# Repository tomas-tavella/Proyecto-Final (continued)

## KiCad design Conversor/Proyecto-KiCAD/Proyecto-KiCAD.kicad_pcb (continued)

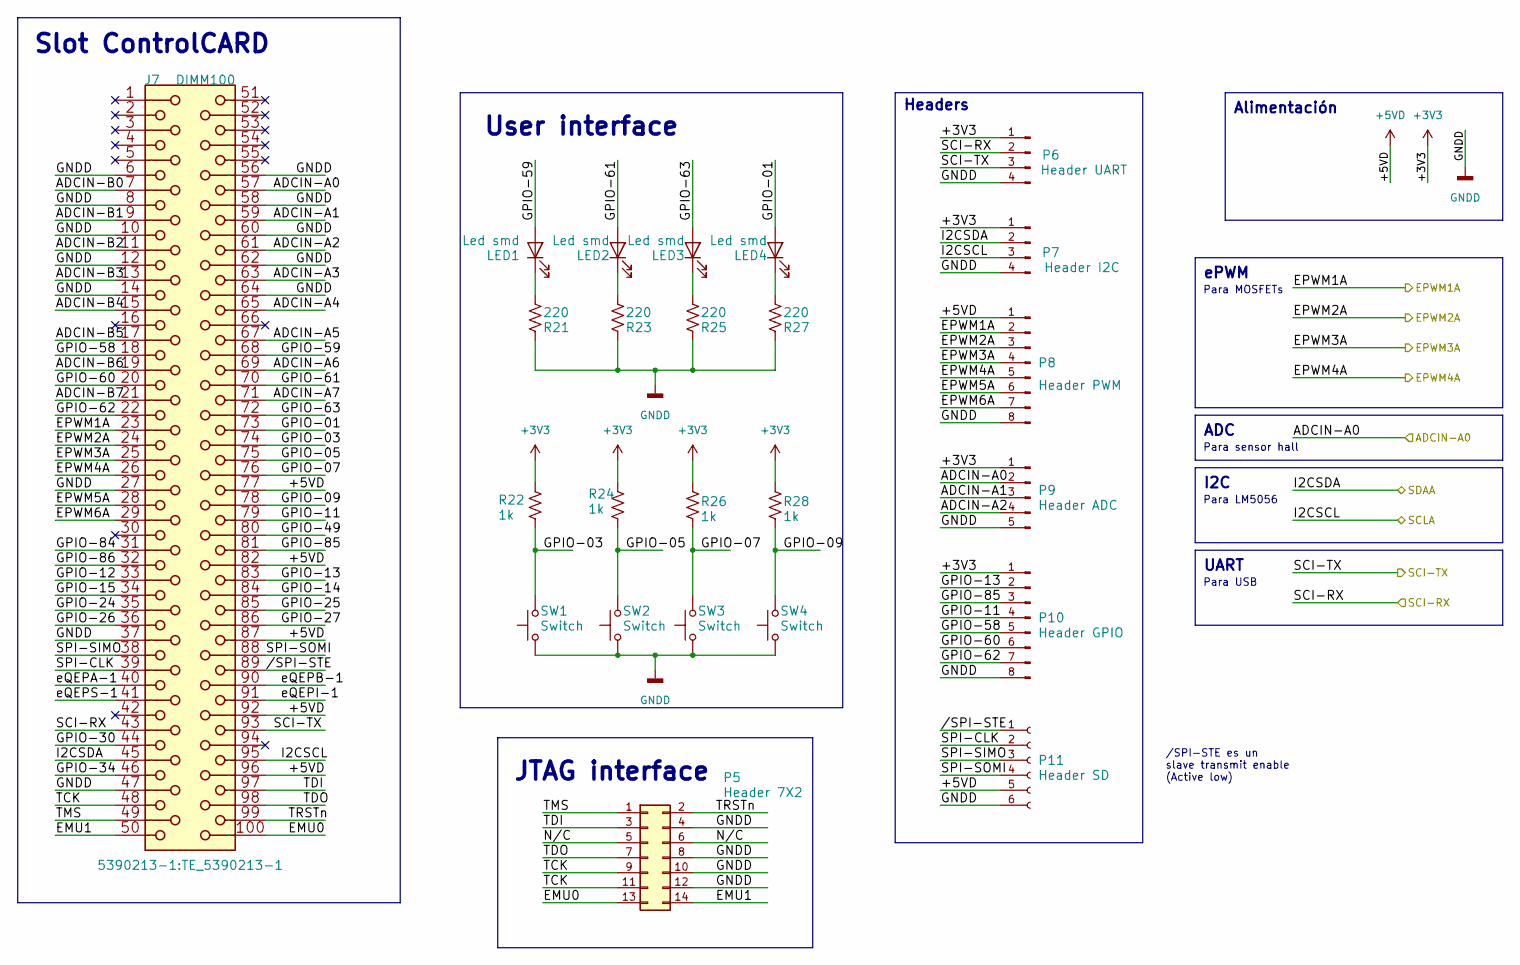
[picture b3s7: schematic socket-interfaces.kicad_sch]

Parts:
J7: DIMM100; TE_5390213-1
LED1, LED2, LED3, LED4: Led smd; D_1206_3216Metric_Pad1.42x1.75mm_HandSolder
P5: Header 7X2; PinSocket_2x07_P2.54mm_Vertical
P6: Header UART; PinHeader_1x04_P2.54mm_Vertical
P7: Header I2C; PinHeader_1x04_P2.54mm_Vertical
P8: Header PWM; PinHeader_1x08_P2.54mm_Vertical
P9: Header ADC; PinHeader_1x05_P2.54mm_Vertical
P10: Header GPIO; PinHeader_1x08_P2.54mm_Vertical
P11: Header SD; PinSocket_1x06_P2.54mm_Horizontal
R21, R23, R25, R27: 220; R_1206_3216Metric_Pad1.30x1.75mm_HandSolder
R22, R24, R26, R28: 1k; R_1206_3216Metric_Pad1.30x1.75mm_HandSolder
SW1, SW2, SW3, SW4: Switch; SW_PUSH_6mm

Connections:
+3V3: P6.1, P7.1, P9.1, P10.1, R22.2, R24.2, R26.2, R28.2; also elsewhere on the board
+5VD: J7.77 (p77), J7.82 (p82), J7.87 (p87), J7.92 (p92), J7.96 (p96), P8.1, P11.5; also elsewhere on the board
/Drivers y Optos/PWM1: J7.23 (p23), P8.2; also elsewhere on the board
/Drivers y Optos/PWM2: J7.24 (p24), P8.3; also elsewhere on the board
/Drivers y Optos//PWM3: J7.25 (p25), P8.4; also elsewhere on the board
/Drivers y Optos//PWM4: J7.26 (p26), P8.5; also elsewhere on the board
/Placa DSP/Socket Interfaces/ADCIN-A0: J7.57 (p57), P9.2; also elsewhere on the board
/Placa DSP/Socket Interfaces/ADCIN-A1: J7.59 (p59), P9.3
/Placa DSP/Socket Interfaces/ADCIN-A2: J7.61 (p61), P9.4
/Placa DSP/Socket Interfaces/ADCIN-A3: J7.63 (p63)
/Placa DSP/Socket Interfaces/ADCIN-A4: J7.65 (p65)
/Placa DSP/Socket Interfaces/ADCIN-A5: J7.67 (p67)
/Placa DSP/Socket Interfaces/ADCIN-A6: J7.69 (p69)
/Placa DSP/Socket Interfaces/ADCIN-A7: J7.71 (p71)
/Placa DSP/Socket Interfaces/ADCIN-B0: J7.7 (p7)
/Placa DSP/Socket Interfaces/ADCIN-B1: J7.9 (p9)
/Placa DSP/Socket Interfaces/ADCIN-B2: J7.11 (p11)
/Placa DSP/Socket Interfaces/ADCIN-B3: J7.13 (p13)
/Placa DSP/Socket Interfaces/ADCIN-B4: J7.15 (p15)
/Placa DSP/Socket Interfaces/ADCIN-B5: J7.17 (p17)
/Placa DSP/Socket Interfaces/ADCIN-B6: J7.19 (p19)
/Placa DSP/Socket Interfaces/ADCIN-B7: J7.21 (p21)
/Placa DSP/Socket Interfaces/EMU0: J7.100 (p100), P5.13
/Placa DSP/Socket Interfaces/EMU1: J7.50 (p50), P5.14
/Placa DSP/Socket Interfaces/EPWM5A: J7.28 (p28), P8.6
/Placa DSP/Socket Interfaces/EPWM6A: J7.29 (p29), P8.7
/Placa DSP/Socket Interfaces/GPIO-01: J7.73 (p73), LED4.2 (A)
/Placa DSP/Socket Interfaces/GPIO-03: J7.74 (p74), R22.1, SW1.2
/Placa DSP/Socket Interfaces/GPIO-05: J7.75 (p75), R24.1, SW2.2
/Placa DSP/Socket Interfaces/GPIO-07: J7.76 (p76), R26.1, SW3.2
/Placa DSP/Socket Interfaces/GPIO-09: J7.78 (p78), R28.1, SW4.2
/Placa DSP/Socket Interfaces/GPIO-11: J7.79 (p79), P10.4
/Placa DSP/Socket Interfaces/GPIO-12: J7.33 (p33)
/Placa DSP/Socket Interfaces/GPIO-13: J7.83 (p83), P10.2
/Placa DSP/Socket Interfaces/GPIO-14: J7.84 (p84)
/Placa DSP/Socket Interfaces/GPIO-15: J7.34 (p34)
/Placa DSP/Socket Interfaces/GPIO-24: J7.35 (p35)
/Placa DSP/Socket Interfaces/GPIO-25: J7.85 (p85)
/Placa DSP/Socket Interfaces/GPIO-26: J7.36 (p36)
/Placa DSP/Socket Interfaces/GPIO-27: J7.86 (p86)
/Placa DSP/Socket Interfaces/GPIO-30: J7.44 (p44)
/Placa DSP/Socket Interfaces/GPIO-34: J7.46 (p46)
/Placa DSP/Socket Interfaces/GPIO-49: J7.80 (p80)
/Placa DSP/Socket Interfaces/GPIO-58: J7.18 (p18), P10.5
/Placa DSP/Socket Interfaces/GPIO-59: J7.68 (p68), LED1.2 (A)
/Placa DSP/Socket Interfaces/GPIO-60: J7.20 (p20), P10.6
/Placa DSP/Socket Interfaces/GPIO-61: J7.70 (p70), LED2.2 (A)
/Placa DSP/Socket Interfaces/GPIO-62: J7.22 (p22), P10.7
/Placa DSP/Socket Interfaces/GPIO-63: J7.72 (p72), LED3.2 (A)
/Placa DSP/Socket Interfaces/GPIO-84: J7.31 (p31)
/Placa DSP/Socket Interfaces/GPIO-85: J7.81 (p81), P10.3
/Placa DSP/Socket Interfaces/GPIO-86: J7.32 (p32)
/Placa DSP/Socket Interfaces/I2CSCL: J7.95 (p95), P7.3; also elsewhere on the board
/Placa DSP/Socket Interfaces/I2CSDA: J7.45 (p45), P7.2; also elsewhere on the board
/Placa DSP/Socket Interfaces/SCI-RX: J7.43 (p43), P6.2; also elsewhere on the board
/Placa DSP/Socket Interfaces/SCI-TX: J7.93 (p93), P6.3; also elsewhere on the board
/Placa DSP/Socket Interfaces/SPI-CLK: J7.39 (p39), P11.2
/Placa DSP/Socket Interfaces/SPI-SIMO: J7.38 (p38), P11.3
/Placa DSP/Socket Interfaces/SPI-SOMI: J7.88 (p88), P11.4
/Placa DSP/Socket Interfaces/TCK: J7.48 (p48), P5.9, P5.11
/Placa DSP/Socket Interfaces/TDI: J7.97 (p97), P5.3
/Placa DSP/Socket Interfaces/TDO: J7.98 (p98), P5.7
/Placa DSP/Socket Interfaces/TMS: J7.49 (p49), P5.1
/Placa DSP/Socket Interfaces/TRSTn: J7.99 (p99), P5.2
/Placa DSP/Socket Interfaces/eQEPA-1: J7.40 (p40)
/Placa DSP/Socket Interfaces/eQEPB-1: J7.90 (p90)
/Placa DSP/Socket Interfaces/eQEPI-1: J7.91 (p91)
/Placa DSP/Socket Interfaces/eQEPS-1: J7.41 (p41)
/Placa DSP/Socket Interfaces//SPI-STE: J7.89 (p89), P11.1
GNDD: J7.6 (p6), J7.8 (p8), J7.10 (p10), J7.12 (p12), J7.14 (p14), J7.27 (p27), J7.37 (p37), J7.47 (p47), J7.56 (p56), J7.58 (p58), J7.60 (p60), J7.62 (p62), J7.64 (p64), P5.4, P5.8, P5.10, P5.12, P6.4, P7.4, P8.8, P9.5, P10.8, P11.6, R21.2, R23.2, R25.2, R27.2, SW1.1, SW2.1, SW3.1, SW4.1; also elsewhere on the board
unnamed: LED1.1 (K), R21.1
unnamed: LED2.1 (K), R23.1
unnamed: LED3.1 (K), R25.1
unnamed: LED4.1 (K), R27.1

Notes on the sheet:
Para LM5056
UART
Para MOSFETs
Para USB
ADC
/SPI-STE es un slave transmit enable (Active low)
Headers
JTAG interface
Slot ControlCARD
I2C
Para sensor hall
ePWM
User interface
Alimentación

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
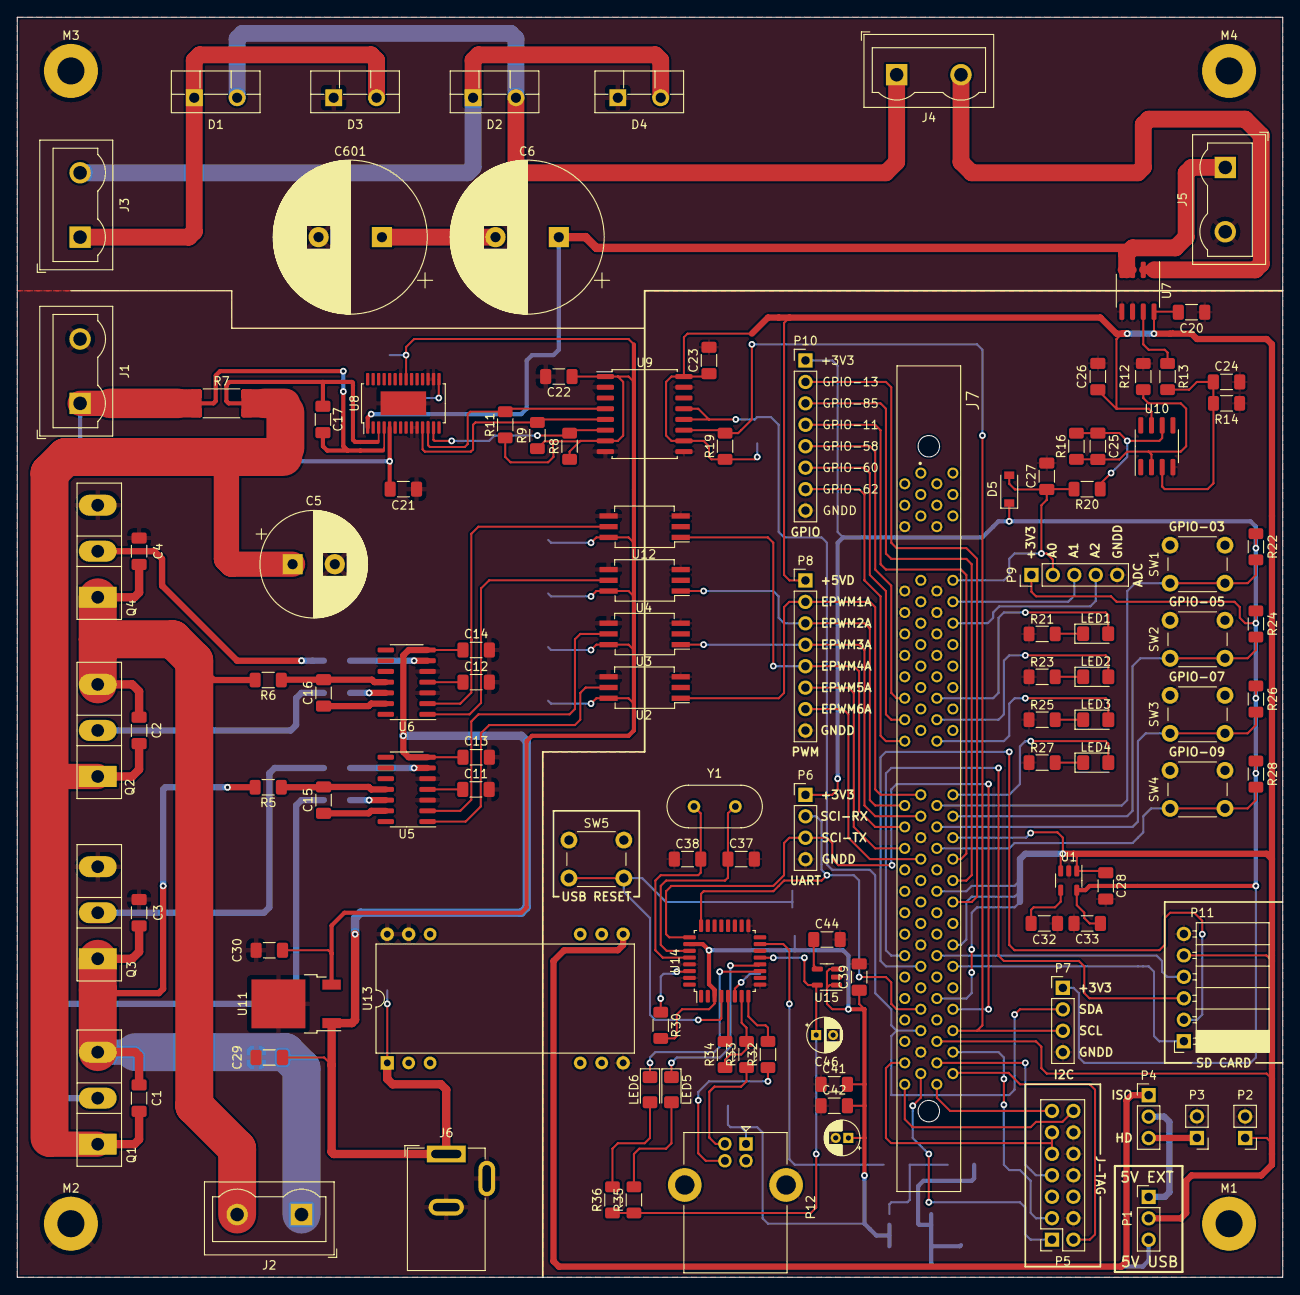
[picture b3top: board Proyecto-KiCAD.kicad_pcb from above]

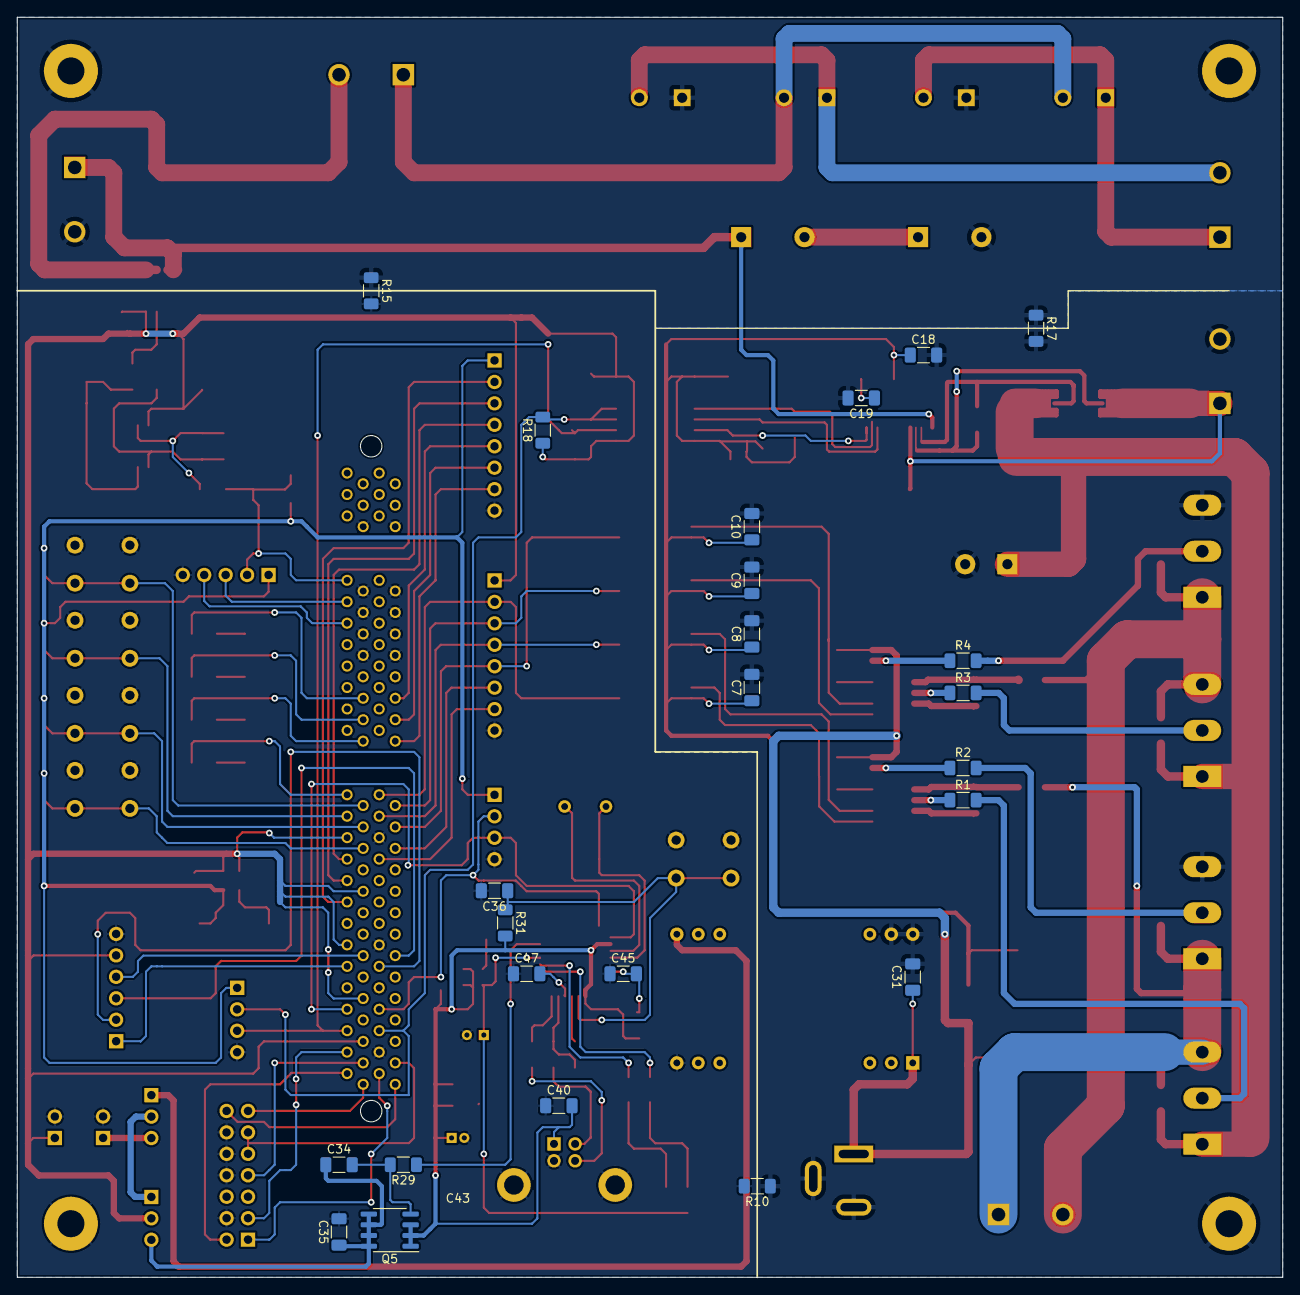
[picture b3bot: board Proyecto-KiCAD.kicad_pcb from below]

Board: 2 copper layers, 149.9 x 149.2 mm, 144 parts (24 on the bottom side), 110 nets.

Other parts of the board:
M1, M2, M3, M4: MountingHole_3.2mm_M3_Pad

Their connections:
GND1: M2.2; also elsewhere on the board
GND2: M3.3, M4.4; also elsewhere on the board
GNDD: M1.1; also elsewhere on the board

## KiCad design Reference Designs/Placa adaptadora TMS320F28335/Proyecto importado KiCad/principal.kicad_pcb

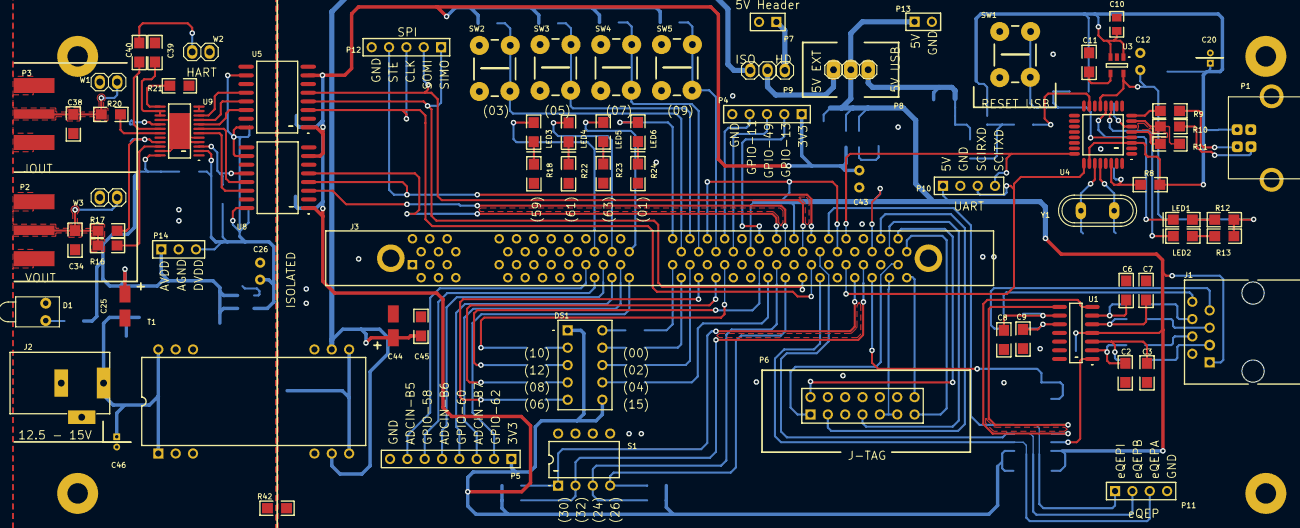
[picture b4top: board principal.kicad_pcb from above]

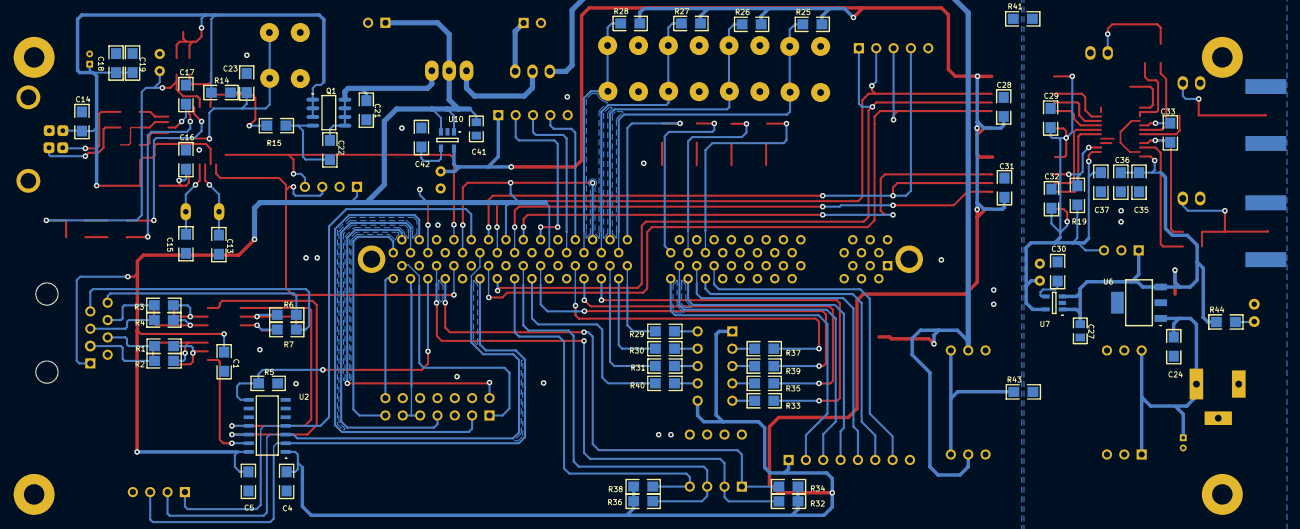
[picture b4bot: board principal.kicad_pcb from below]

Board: 2 copper layers, 137 parts (60 on the bottom side), 125 nets.

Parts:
C1, C2, C3, C4, C5, C6, C7, C8, C9, C11, C13, C14, C15, C16, C17, C18, C19, C21, C22, C23, C24, C28, C29, C30, C31, C32, C33, C34, C35, C36, C37, C38, C39, C40, C42, C45: Capacitor; C 1206
C10, C27, C41: Capacitor; 0805
C12, C26, C43: Tantalum capacitor; Tantalum
C20, C46: Capacitor polarzado; CAP4x7x1.5mm
C25, C44: Capacitor polarzado; Almn cap
D1: Typical RED GaAs LED; LED-1
DS1: 7.62 mm Black Surface Orange 7-Segment Display: C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; A
J1: RJ-45 connector, 8-pins, ethernet; 15-43-6588
J2: jack
J3: Vertical, DIMM 2P Low Insertion Force, 100 Positi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; 390213-1
LED1: LED red; LED 1206
LED2: LED green; LED 1206
LED3, LED5: Led green; LED 1206
LED4, LED6: Led yellow; LED 1206
P1: Conector USB tipo B; USBB
P2, P3: sma
P4, P12: Header, 5-Pin; HDR1X5
P5: Header, 8-Pin; HDR1X8
P6: Header, 7-Pin, Dual row; HDR2X7
P7, P13: Header, 2-Pin; HDR1X2
P8: Toggle sw
P9: Jumper 2
P10, P11: Header, 4-Pin; HDR1X4
P14: Header, 3-Pin; HDR1X3
Q1: HEXFET Power MOSFET; SO-8_L
R1, R2, R3, R4, R5, R6, R7, R8, R9, R10, R11, R12, R13, R14, R15, R16, R17, R18, R19, R20, R21, R22, R23, R24, R25, R26, R27, R28, R29, R30, R31, R32, R33, R34, R35, R36, R37, R38, R39, R40, R41, R42, R43, R44: Resistencia; R 1206
S1: DIP Switch; DIP-8
SW1, SW2, SW3, SW4, SW5: TACT SW
T1: DIL24
U1: Low Power Quad Operational Amplifier, 14-pin Narr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; M14A_N
U2: IC VOLT-LEVEL TRANSLATOR 14-SOIC; SOIC-14
U3, U7, U10: Single Output Low Noise LDO, 150 mA, Fixed 3.3 V 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; TI-DBV5_N
U4: USB UART Asynchronous Serial Data Transfer Chip, 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; LQFP-32_N
U5, U8: 150 Mbps 6 kVpk Low Power Quad Channels, Digital 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; DW0016A_N
U6: DCY4
U9: DAC8760; PWP
W1, W2, W3: Jumper Wire; Jumper
Y1: Cristal de 6Mhz; Y TRHU

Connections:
3V3: C4.2, C28.1, C31.1, C43.1, DS1.1, DS1.6, P4.1, P5.1, R25.2, R26.2, R27.2, R28.2, R32.1, R34.1, R36.1, R38.1, U2.1, U5.1, U5.7, U8.1, U8.7, U10.5
3V3OUT: C17.2, U4.6
5V: C1.2, C5.1, C41.1, J1.1, J3.77, J3.82, J3.87, J3.92, J3.96, P8.2, P10.1, P13.1, U1.4, U2.14, U10.1, U10.3
5V HEADER: P7.1, P9.3
5V SUPPLY: C44.1, C45.2, P9.1, T1.11, T1.14
5V USB: C21.1, C22.1, P8.1, Q1.5, Q1.6, Q1.7, Q1.8
+VSENSE: R16.2, U9.22
A: U1.1, U2.13
A+: J1.3, R2.2
A-: J1.4, R1.2
ADCIN-B5: J3.17, P5.7
ADCIN-B6: J3.19, P5.5
ADCIN-B7: J3.21, P5.3
AGND: C24.1, C25.2, C26.2, C27.1, C29.2, C30.2, C32.2, C34.2, C35.2, C36.2, C37.2, C38.2, C39.2, C46.2, D1.2, J2.2, J2.3, P2.2, P3.2, P14.2, R21.2, R41.2, R42.2, R43.1, U5.9, U5.15, U6.2, U6.4, U7.2, U8.9, U8.15, U9.1, U9.4, U9.5, U9.11, U9.12, U9.16, U9.23, U9.25, W1.2, W2.2, W3.2
AGND1: R43.2, T1.12, T1.13
ALARM#: R19.2, U8.12, U9.3
AVCC: C16.2, R8.2, U4.30
AVDD: C25.1, C27.2, C35.1, C36.1, P14.1, R44.2, U6.3, U7.1, U7.3, U9.24
B: U1.7, U2.12
B+: J1.5, R4.2
B-: J1.6, R3.2
CLR: U8.14, U9.6
CS#: U8.13, U9.7
DM: P1.2, R9.2
DP: P1.3, R10.2
DVDD: C26.1, C29.1, C32.1, C37.1, P14.3, R19.1, U5.10, U5.16, U7.5, U8.10, U8.16, U9.2
EMU0: J3.100, P6.13
EMU1: J3.50, P6.14
EQEPA-1: J3.40, P11.3, U2.2
EQEPB-1: J3.90, P11.2, U2.3
EQEPI-1: J3.91, P11.1, U2.4
EXTERN 5V: P8.3, P9.2
FA+: C3.2, R2.1, U1.3
FA-: C2.1, R1.1, U1.2
FB+: C7.2, R4.1, U1.5
FB-: C6.1, R3.1, U1.6
FZ+: C9.2, R7.1, U1.10
FZ-: C8.1, R6.1, U1.9
GND: C1.1, C2.2, C3.1, C4.1, C5.2, C6.2, C7.1, C8.2, C9.1, C10.2, C11.2, C12.2, C13.2, C14.2, C15.2, C16.1, C17.1, C18.1, C19.1, C20.2, C21.2, C23.2, C28.2, C31.2, C41.2, C42.2, C43.2, C44.2, C45.1, J1.2, J3.6, J3.8, J3.10, J3.12, J3.14, J3.27, J3.37, J3.47, J3.56, J3.58, J3.60, J3.62, J3.64, P1.0, P1.4, P4.5, P5.8, P6.4, P6.8, P6.10, P6.12, P7.2, P10.2, P11.4, P12.5, P13.2, R5.1, R18.2, R22.2, R23.2, R24.2, R41.1, R42.1, S1.5, S1.6, S1.7, S1.8, SW1.1, SW2.1, SW3.1, SW4.1, SW5.1, T1.10, T1.15, U1.11, U2.7, U3.2, U4.9, U4.14, U4.17, U4.29, U4.31, U5.2, U5.8, U8.2, U8.8, U10.2
GPIO-00: J3.23, R29.1
GPIO-01: J3.73, LED6.1
GPIO-02: J3.24, R30.1
GPIO-03: J3.74, R25.1, SW2.2
GPIO-04: J3.25, R31.1
GPIO-05: J3.75, R26.1, SW3.2
GPIO-06: J3.26, R33.1
GPIO-07: J3.76, R27.1, SW4.2
GPIO-08: J3.28, R35.1
GPIO-09: J3.78, R28.1, SW5.2
GPIO-10: J3.29, R37.1
GPIO-11: J3.79, P4.4
GPIO-12: J3.33, R39.1
GPIO-13: J3.83, P4.2
GPIO-15: J3.34, R40.1
GPIO-24: J3.35, R36.2, S1.3
GPIO-25: J3.85, U8.5
GPIO-26: J3.36, R38.2, S1.4
GPIO-27: J3.86, U8.3
GPIO-30: J3.44, R32.2, S1.1
GPIO-32: J3.45, R34.2, S1.2
GPIO-34: J3.46, R5.2, U2.8
GPIO-49: J3.80, P4.3
GPIO-58: J3.18, P5.6
GPIO-59: J3.68, LED3.1
GPIO-60: J3.20, P5.4
GPIO-61: J3.70, LED4.1
GPIO-62: J3.22, P5.2
GPIO-63: J3.72, LED5.1
HART-IN: C40.1, U9.18
IOUT: R20.2, U9.19
MISO: U5.12, U9.10
MOSI: U5.13, U9.9
NetC11_1: C11.1, U3.4
NetC22_2: C22.2, Q1.4, R15.2
NetC30_1: C30.1, U7.4
NetC33_2: C33.2, U9.17
NetC34_1: C34.1, P2.1, R16.1, R17.1, W3.1
NetC38_1: C38.1, P3.1, R20.1, W1.1
NetC40_2: C40.2, W2.1
NetC42_1: C42.1, U10.4
NetD1_1: D1.1, R44.1
NetDS1_2: DS1.2, R37.2
NetDS1_3: DS1.3, R39.2
NetDS1_4: DS1.4, R35.2
NetDS1_5: DS1.5, R33.2
NetDS1_7: DS1.7, R40.2
NetDS1_8: DS1.8, R31.2
NetDS1_9: DS1.9, R30.2
NetDS1_10: DS1.10, R29.2
NetLED1_1: LED1.1, R12.2
NetLED2_1: LED2.1, R13.2
NetLED3_2: LED3.2, R18.1
NetLED4_2: LED4.2, R22.1
NetLED5_2: LED5.2, R23.1
NetLED6_2: LED6.2, R24.1
NetR21_1: R21.1, U9.13
PWREN#: R15.1, U4.15
REFIN: C39.1, U9.14, U9.15
RESET#: C23.1, R14.1, SW1.2, U4.4
RSTOUT#: R11.1, U4.5
RXD: J3.93, P10.4, U4.24
RXLED#: LED2.2, U4.11
SCIRX-A: J3.43, P10.3, U4.25
SCLK: U5.14, U9.8
SPICLK-A: J3.39, P12.3, U5.3
SPISIMO-A: J3.38, P12.1, U5.4
SPISOMI-A: J3.88, P12.2, U5.5
SPISTE-A: J3.89, P12.4, U8.4
SUPPLY: C24.2, C46.1, J2.1, T1.1, T1.24, U6.1
TCK: J3.48, P6.9, P6.11
TDI: J3.97, P6.3
TDO: J3.98, P6.7
TMS: J3.49, P6.1
TRSTN: J3.99, P6.2
TXLED#: LED1.2, U4.12
U5V: C10.1, C14.1, C18.2, C19.2, C20.1, P1.1, Q1.1, Q1.2, Q1.3, R8.1, R14.2, U3.1, U3.3, U4.3, U4.26
USBDM: R9.1, U4.8
USBDP: R10.1, R11.2, U4.7
VCCIO: C12.1, R12.1, R13.1, U3.5, U4.13
VOUT: C33.1, R17.2, U9.21
XTIN: C13.1, U4.27, Y1.1
XTOUT: C15.1, U4.28, Y1.2
Z: U1.8, U2.11
Z+: J1.7, R7.2
Z-: J1.8, R6.2

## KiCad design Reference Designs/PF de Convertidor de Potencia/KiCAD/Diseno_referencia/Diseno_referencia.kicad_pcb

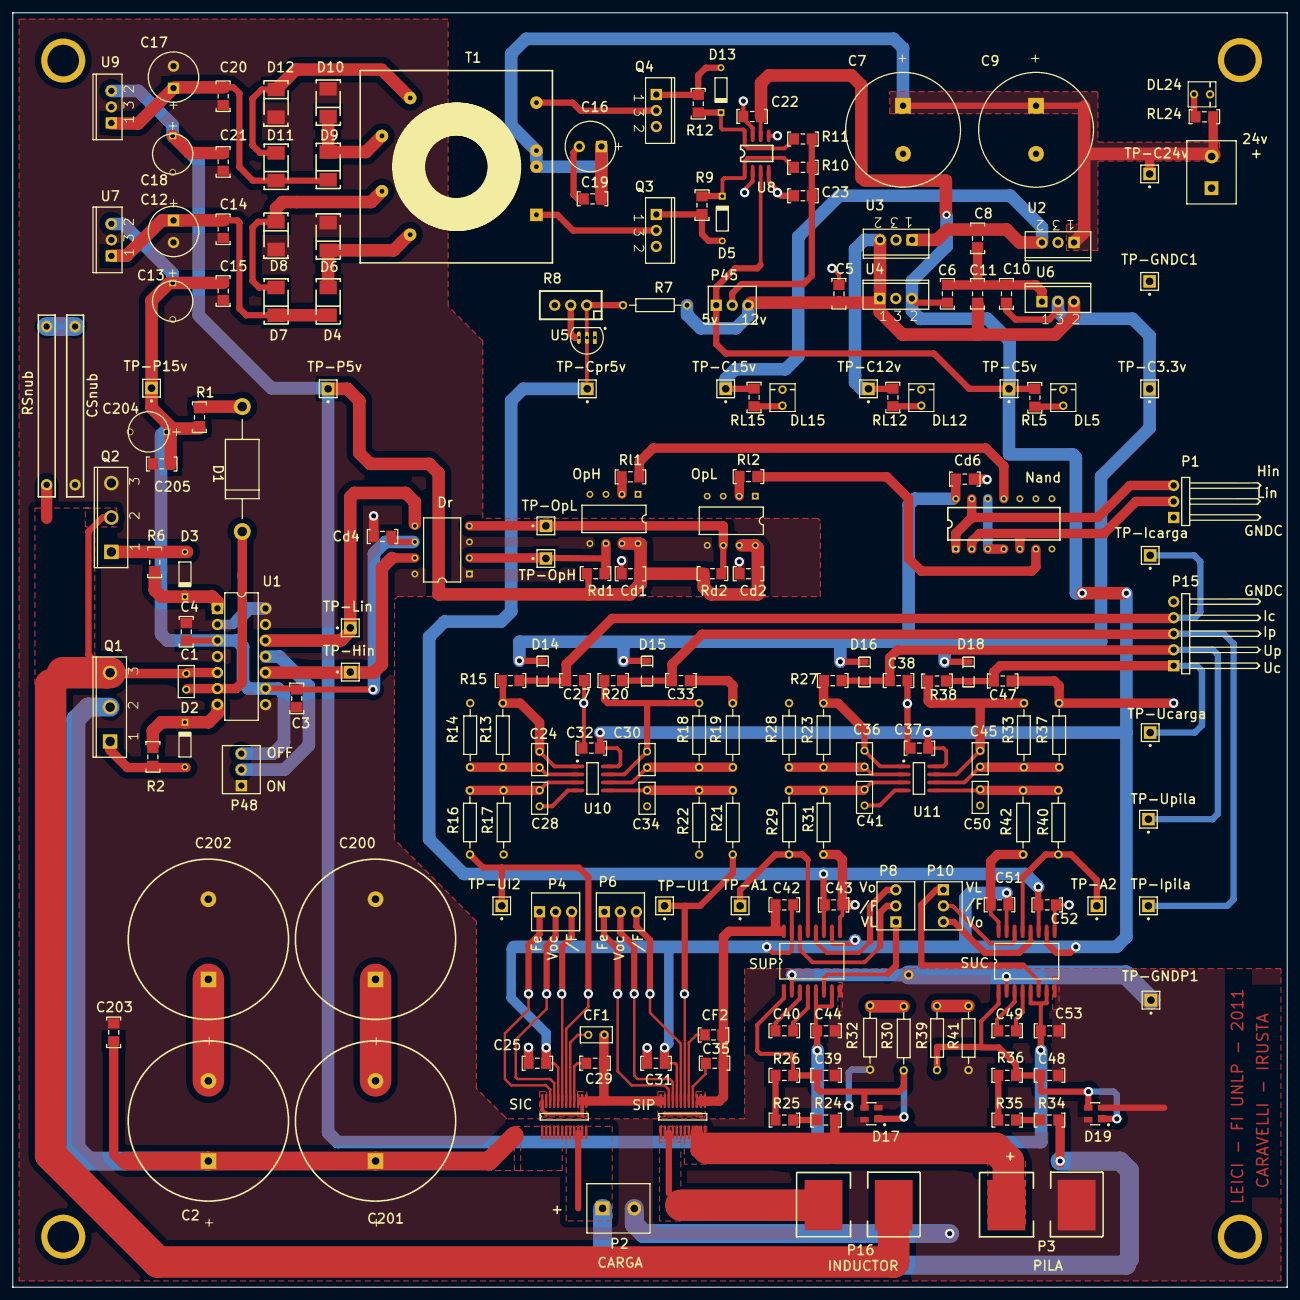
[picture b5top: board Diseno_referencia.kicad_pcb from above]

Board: 2 copper layers, 202.0 x 202.0 mm, 193 parts (0 on the bottom side), 102 nets.

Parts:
24v: Alimentacion 24v; HDR1X2-POT*
C1: CapBootstrap; RAD-0.1
C2, C200, C201, C202: Cap Pol1; RB12.7-25*
C3: Cap3; 8-1206
C4, C203, C205: Cap4; 8-1206
C5: Cap5; 8-1206
C6: Cap6; 8-1206
C7, C9: Cap Pol1; RB7.6-18.2*
C8: Cap8; 8-1206
C10: Cap10; 8-1206
C11: Cap11; 8-1206
C12, C16, C17: Cap Pol1; RB3.5-8*
C13, C18, C204: Cap Pol1; RB5.8-6.4*
C14: Cap14; 8-1206
C15: Cap15; 8-1206
C19: Cap19; 8-1206
C20: Cap20; 8-1206
C21: Cap21; 8-1206
C22: Cap22; 8-1206
C23: Cap23; 8-1206
C24: Cap24; RAD-0.1
C25: Cap25; 8-1206
C27: Cap27; 8-1206
C28: Cap28; RAD-0.1
C29: Cap29; 8-1206
C30: Cap30; RAD-0.1
C31: Cap31; 8-1206
C32: Cap32; 8-1206
C33: Cap33; 8-1206
C34: Cap34; RAD-0.1
C35: Cap35; 8-1206
C36: Cap36; RAD-0.1
C37: Cap37; 8-1206
C38: Cap38; 8-1206
C39: Cap39; 8-1206
C40: Cap40; 8-1206
C41: Cap41; RAD-0.1
C42: Cap42; 8-1206
C43: Cap43; 8-1206
C44: Cap44; 8-1206
C45: Cap45; RAD-0.1
C47: Cap47; 8-1206
C48: Cap48; 8-1206
C49: Cap49; 8-1206
C50: Cap50; RAD-0.1
C51: Cap51; 8-1206
C52: Cap52; 8-1206
C53: Cap53; 8-1206
CF1: CapF1; RAD-0.1
CF2: CapF2; 8-1206
CSnub: CapSnub; FOOTSNUB
Cd1: Capd1; 8-1206
Cd2, Cd4, Cd6: Capd2; 8-1206
D1: MUR160 (460); CASE 267*
D2, D3, D5, D13: Diode 1N4148; DO-35
D4, D6, D7, D8, D9, D10, D11, D12: MBR0540; CASE403A*
D14, D15, D16, D18: BAT54; SOD123*
D17, D19: BAS28; SOT-143*
DL5: LED4; LED-1*V
DL12: LED3; LED-1*V
DL15: LED2; LED-1*V
DL24: LED1; LED-1*
Dr: TC4427; TC4424-DIP8
Nand: 74HCT00; MM74HC00_GON
OpH: 6N137
OpL: 6N137
P1: Header 3H; HDR1X3H*
P2: Header 2; HDR1X2-POT*
P3, P16: Header 2; IND-CONECTOR
P4, P6, P8, P10: Header 3; HDR1X3*
P15: Header 5; HDR1X5H*
P45: Header 3; JUMPER
P48: Header 10; JUMPER
Q1, Q2: IRFP250; TO-247AC
Q3, Q4: IRF7380; TO220-MOS
R1: Rbootstrap; 8-1206 - RES
R2: Res2; 8-1206 - RES
R6: Res6; 8-1206 - RES
R7: Res7; AXIAL-0.4
R8: RPot; VR*
R9: Res9; 8-1206 - RES
R10: Res10; 8-1206 - RES
R11: Res11; 8-1206 - RES
R12: Res12; 8-1206 - RES
R13: Res13; AXIAL-0.4
R14: Res14; AXIAL-0.4
R15: Res15; 8-1206 - RES
R16: Res16; AXIAL-0.4
R17: Res17; AXIAL-0.4
R18: Res18; AXIAL-0.4
R19: Res19; AXIAL-0.4
R20: Res20; 8-1206 - RES
R21: Res21; AXIAL-0.4
R22: Res22; AXIAL-0.4
R23: Res23; AXIAL-0.4
R24: Res24; 8-1206 - RES
R25: Res25; 8-1206 - RES
R26: Res26; 8-1206 - RES
R27: Res27; 8-1206 - RES
R28: Res28; AXIAL-0.4
R29: Res29; AXIAL-0.4
R30: Res30; AXIAL-0.4
R31: Res31; AXIAL-0.4
R32: Res32; AXIAL-0.4
R33: Res33; AXIAL-0.4
R34: Res34; 8-1206 - RES
R35: Res35; 8-1206 - RES
R36: Res36; 8-1206 - RES
R37: Res37; AXIAL-0.4
R38: Res38; 8-1206 - RES
R39: Res39; AXIAL-0.4
R40: Res40; AXIAL-0.4
R41: Res41; AXIAL-0.4
R42: Res42; AXIAL-0.4
RL5: ResL5; 8-1206 - RES
RL12: ResL12; 8-1206 - RES
RL15: ResL15; 8-1206 - RES
RL24: ResL24; 8-1206 - RES
RSnub: ResSnub; FOOTSNUB
Rd1: Rd1; 8-1206 - RES
Rd2: Rd2; 8-1206 - RES
Rl1, Rl2: Rd1; 8-1206 - RES
SIC: SI 1 20BB; SENSOR CORRIENTE ACS 709
SIP: SI 1 20BB; SENSOR CORRIENTE ACS 709
SUC: S2; SENS TENSION HCPL-788J
SUP: S1; SENS TENSION HCPL-788J
T1: Trans BB; TRAFO-2PRI-2SEC
TP-A1, TP-A2: PIN1
TP-C3.3v, TP-C5v, TP-C12v, TP-C15v, TP-C24v: PIN1
TP-Cpr5v: PIN1
TP-GNDC1: PIN1
TP-GNDP1: PIN1
TP-Hin: PIN1
TP-Icarga: PIN1
TP-Ipila: PIN1
TP-Lin: PIN1
TP-OpH: PIN1
TP-OpL: PIN1
TP-P5v, TP-P15v: PIN1
TP-UI1, TP-UI2: PIN1
TP-Ucarga: PIN1
TP-Upila: PIN1
U1: IR2110; PDIP14
U2, U7: MC7815ACT; TO220*
U3: MC7812ACT; TO220*
U4, U9: MC7805ACT; TO220*
U5: LM336BZ-5.0; Z03A
U6: MC7833ACT; TO220*
U8: MAX845; SO-8
U10, U11: TLC2272; 751-02_N

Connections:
C_3.3V: C10.1, Cd6.1, D14.2, D15.2, D16.2, D18.2, Nand.14, TP-C3.3v.1, U6.3
C_5V: C6.1, C22.2, C25.1, C31.1, C32.1, C37.1, C42.2, C51.2, P45.1, RL5.2, SIC.20, SIP.20, SUC.10, SUC.15, SUP.10, SUP.15, TP-C5v.1, U4.2, U8.3, U8.6, U10.8, U11.8
C_12V: C5.1, C11.1, P45.3, R7.2, RL12.2, TP-C12v.1, U3.2, U4.1, U6.2
C_15V: C8.1, RL15.2, TP-C15v.1, U2.2, U3.1
C_24V: 24v.2, C7.1, C9.1, C16.1, C19.2, RL24.2, T1.2, T1.3, TP-C24v.1, U2.1
C_PREC_5V: C43.2, C52.2, R7.1, R8.1, SUC.11, SUP.11, TP-Cpr5v.1, U5.2
GNDC: 24v.1, C5.2, C6.2, C7.2, C8.2, C9.2, C10.2, C11.2, C16.2, C19.1, C22.1, C23.2, C25.2, C27.2, C28.2, C29.2, C31.2, C32.2, C33.2, C34.2, C35.2, C37.2, C38.2, C41.2, C42.1, C43.1, C47.2, C50.2, C51.1, C52.1, CF1.1, CF2.1, Cd6.2, DL5.2, DL12.2, DL15.2, DL24.2, Nand.7, Nand.9, Nand.10, OpH.1, OpH.3, OpH.4, OpL.1, OpL.3, OpL.4, P1.1, P15.5, Q3.3, Q4.3, R8.3, R14.1, R17.2, R19.1, R22.2, R28.1, R31.2, R37.1, R42.2, SIC.13, SIC.14, SIC.15, SIC.23, SIC.24, SIP.13, SIP.14, SIP.15, SIP.23, SIP.24, SUC.9, SUC.16, SUP.9, SUP.16, TP-GNDC1.1, U2.3, U3.3, U4.3, U5.1, U6.1, U8.2, U8.4, U8.5, U8.7, U10.4, U11.4
GNDP: C3.2, C4.2, C12.2, C13.2, C14.1, C15.1, C17.2, C18.2, C20.1, C21.1, C39.2, C44.2, C48.2, C53.2, C200.2, C202.2, C203.2, C204.2, C205.2, CSnub.2, Cd1.2, Cd2.2, Cd4.2, D6.1, D8.1, D10.1, D12.1, D17.2, D17.4, D19.2, D19.4, Dr.1, Dr.3, Dr.8, OpH.5, OpL.5, P2.2, P3.2, P48.1, Q2.3, R32.2, R41.2, SUC.2, SUC.8, SUP.2, SUP.8, TP-GNDP1.1, U1.2, U1.4, U1.8, U1.13, U1.14, U7.3, U9.3
NetC1_1: C1.1, D1.2, U1.6
NetC1_2: C1.2, P16.2, Q1.3, Q2.2, RSnub.2, U1.5
NetC2_1: C2.1, C201.1, C203.1, Q1.2, SIC.1, SIC.2, SIC.3, SIC.4, SIC.5, SIC.6
NetC2_2: C2.2, C202.1
NetC12_1: C12.1, C14.2, D4.2, D7.2, U7.1
NetC17_1: C17.1, C20.2, D9.2, D11.2, U9.1
NetC23_1: C23.1, P45.2, R10.2, R11.1
NetC24_1: C24.1, R13.1, R14.2, U10.2
NetC24_2: C24.2, R13.2, R15.1, U10.1
NetC27_1: C27.1, D14.1, P15.4, R15.2, TP-Icarga.1
NetC28_1: C28.1, R16.2, R17.1, U10.3
NetC29_1: C29.1, SIC.16
NetC30_1: C30.1, R18.1, R19.2, U10.6
NetC30_2: C30.2, R18.2, R20.1, U10.7
NetC33_1: C33.1, D15.1, P15.3, R20.2, TP-Ipila.1
NetC34_1: C34.1, R21.2, R22.1, U10.5
NetC35_1: C35.1, SIP.16
NetC36_1: C36.1, R23.1, R28.2, U11.2
NetC36_2: C36.2, R23.2, R27.1, U11.1
NetC38_1: C38.1, D16.1, P15.2, R27.2, TP-Upila.1
NetC39_1: C39.1, D17.1, D17.3, R26.2, R30.1, SUP.1
NetC40_1: C40.1, SUP.3
NetC40_2: C40.2, SUP.4
NetC41_1: C41.1, R29.2, R31.1, U11.3
NetC45_1: C45.1, R33.1, R37.2, U11.6
NetC45_2: C45.2, R33.2, R38.1, U11.7
NetC47_1: C47.1, D18.1, P15.1, R38.2, TP-Ucarga.1
NetC48_1: C48.1, D19.1, D19.3, R36.2, R39.1, SUC.1
NetC49_1: C49.1, SUC.3
NetC49_2: C49.2, SUC.4
NetC50_1: C50.1, R40.2, R42.1, U11.5
NetC200_1: C200.1, C201.2
NetCF1_2: CF1.2, SIC.17
NetCF2_2: CF2.2, SIP.17
NetCsnub_1: CSnub.1, RSnub.1
NetD1_1: D1.1, R1.2
NetD2_1: D2.1, Q1.1, R2.2
NetD2_2: D2.2, R2.1, U1.7
NetD3_1: D3.1, Q2.1, R6.2
NetD3_2: D3.2, R6.1, U1.1
NetD4_1: D4.1, D6.2, T1.5
NetD5_1: D5.1, Q3.1, R9.2
NetD5_2: D5.2, R9.1, R10.1, U8.1
NetD7_1: D7.1, D8.2, T1.6
NetD9_1: D9.1, D10.2, T1.7
NetD11_1: D11.1, D12.2, T1.8
NetD13_1: D13.1, Q4.1, R12.2
NetD13_2: D13.2, R11.2, R12.1, U8.8
NetDL5_1: DL5.1, RL5.1
NetDL12_1: DL12.1, RL12.1
NetDL15_1: DL15.1, RL15.1
NetDL24_1: DL24.1, RL24.1
NetDr_2: Dr.2, OpH.6, Rd1.2, TP-OpH.1
NetDr_4: Dr.4, OpL.6, Rd2.2, TP-OpL.1
NetDr_5: Dr.5, TP-Lin.1, U1.12
NetDr_7: Dr.7, TP-Hin.1, U1.10
NetNand_1: Nand.1, Nand.13, P1.3
NetNand_2: Nand.2, Nand.5, P1.2
NetNand_3: Nand.3, Nand.4, Nand.12
NetNand_6: Nand.6, Rl2.1
NetNand_11: Nand.11, Rl1.1
NetOpH_2: OpH.2, Rl1.2
NetOpL_2: OpL.2, Rl2.2
NetP2_1: P2.1, R34.1, SIC.7, SIC.8, SIC.9, SIC.10, SIC.11, SIC.12
NetP3_1: P3.1, R24.1, SIP.7, SIP.8, SIP.9, SIP.10, SIP.11, SIP.12
NetP4_1: P4.1, SIC.22
NetP4_2: P4.2, SIC.21
NetP4_3: P4.3, SIC.19
NetP6_1: P6.1, SIP.22
NetP6_2: P6.2, SIP.21
NetP6_3: P6.3, SIP.19
NetP8_1: P8.1, SUP.6
NetP8_2: P8.2, SUP.14
NetP8_3: P8.3, SUP.12
NetP10_1: P10.1, SUC.6
NetP10_2: P10.2, SUC.14
NetP10_3: P10.3, SUC.12
NetP16_1: P16.1, SIP.1, SIP.2, SIP.3, SIP.4, SIP.5, SIP.6
NetP48_2: P48.2, U1.11
NetQ3_2: Q3.2, T1.1
NetQ4_2: Q4.2, T1.4
NetR8_2: R8.2, U5.3
NetR16_1: R16.1, SIC.18, TP-UI2.1
NetR21_1: R21.1, SIP.18, TP-UI1.1
NetR24_2: R24.2, R25.1
NetR25_2: R25.2, R26.1
NetR29_1: R29.1, SUP.13, TP-A1.1
NetR30_2: R30.2, R32.1
NetR34_2: R34.2, R35.1
NetR35_2: R35.2, R36.1
NetR39_2: R39.2, R41.1
NetR40_1: R40.1, SUC.13, TP-A2.1
P_5V: C18.1, C21.2, C44.1, C53.1, Cd1.1, Cd2.1, OpH.7, OpH.8, OpL.7, OpL.8, Rd1.1, Rd2.1, SUC.5, SUC.7, SUP.5, SUP.7, TP-P5v.1, U9.2
P_15V: C3.1, C4.1, C13.1, C15.2, C204.1, C205.1, Cd4.1, Dr.6, P48.3, R1.1, TP-P15v.1, U1.3, U1.9, U7.2
